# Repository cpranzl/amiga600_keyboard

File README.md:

# amiga600_keyboard
A replacement for the Amiga 600 keyboard

## Measurements

## OpenSCAD
linear_extrude(50){
    polygon(points=[[0,0],
                    [0,1245],
                    [3240,1240],
                    [3240,1005],
                    [3040,1005],
                    [3040,525],
                    [3240,525],
                    [3240,0]]
    );
}

## KiCAD

 40,  40   -  40, 164.5
 40, 164.5 - 364, 164.5
364, 164.5 - 364, 140.5
364, 140.5 - 344, 140.5
344, 140.5 - 344,  92.5
344,  92.5 - 364,  92.5
364,  92.5 - 364,  40
364,  40   -  40,  40

# Key Placement

Row 00  50.038
Row 01  78.994
Row 02  98.044
Row 03 117.094
Row 04 136.144
Row 05 155.067

Esc    57.023,  50.038
Help  347.472,  50.038
Del   350.012,  78.994
Up    330.581, 136.144
Left  311.531, 155.067
Down  330.581, 155.067
Right 349.631, 155.067

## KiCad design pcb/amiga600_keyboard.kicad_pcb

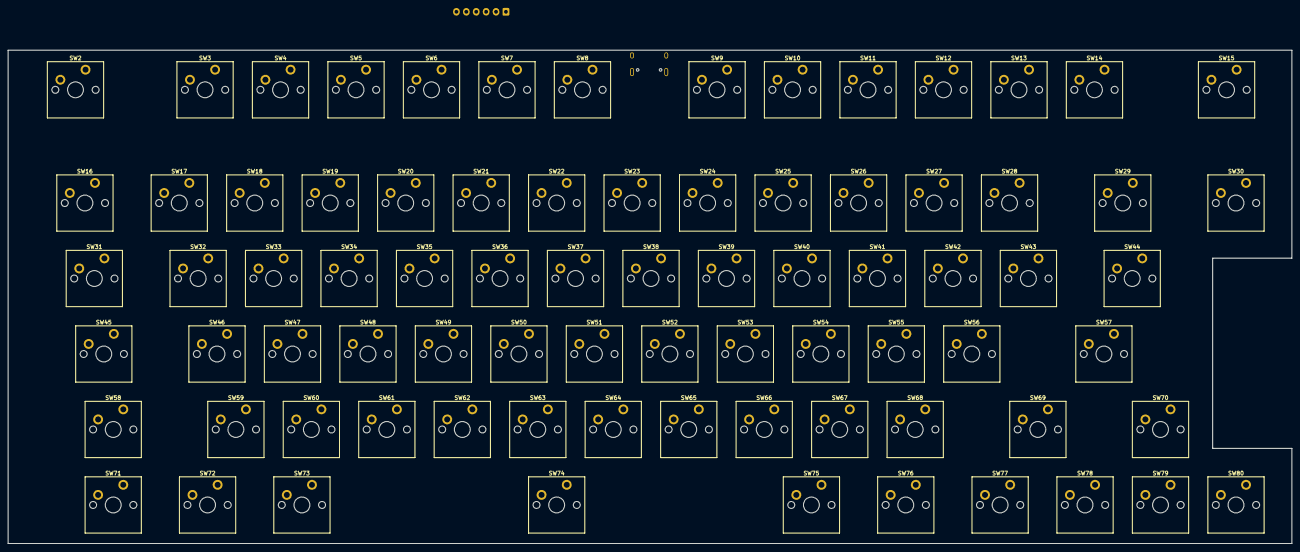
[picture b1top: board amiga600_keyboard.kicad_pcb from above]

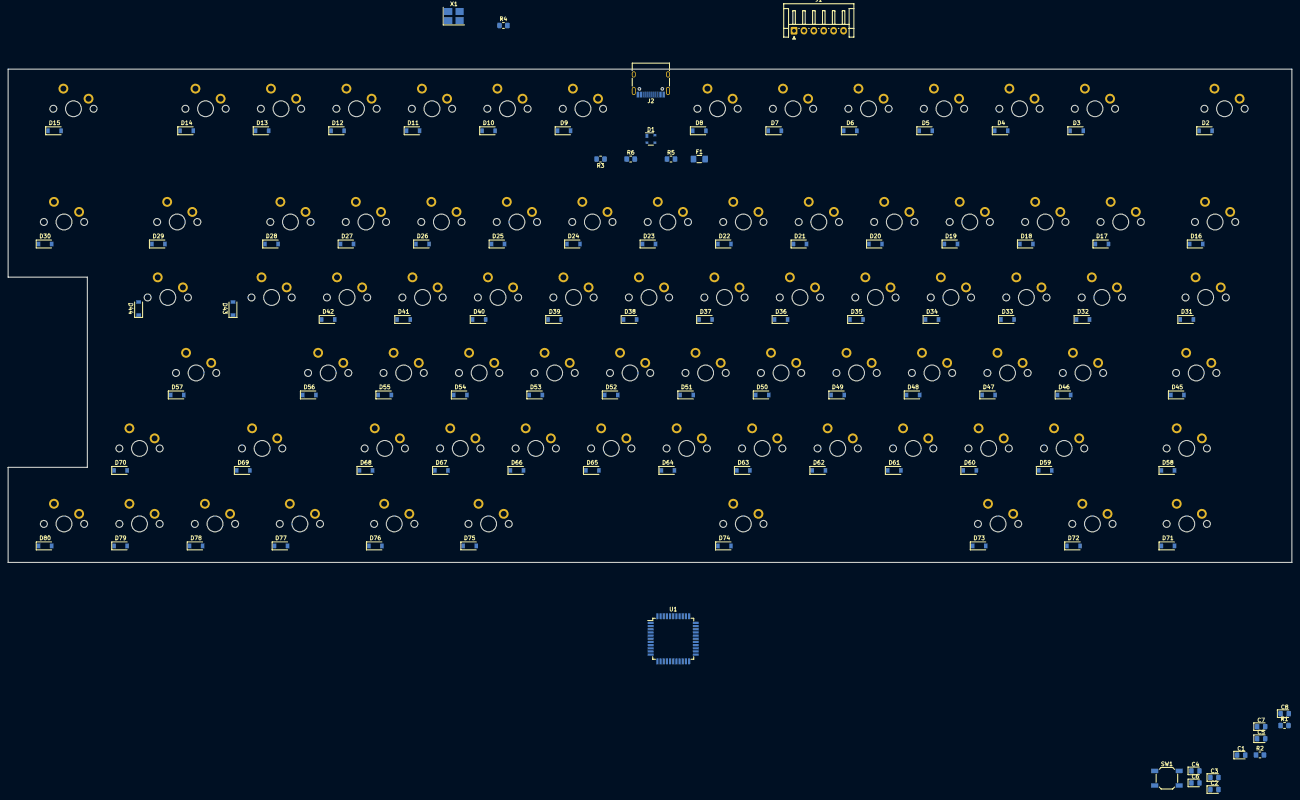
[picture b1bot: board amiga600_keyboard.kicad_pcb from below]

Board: 2 copper layers, 324.0 x 124.5 mm, 179 parts (100 on the bottom side), 117 nets, no tracks yet.

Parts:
C1, C2: 22p; D_0805_2012Metric_Pad1.15x1.40mm_HandSolder
C3, C4, C6, C7, C8: 0.1u; D_0805_2012Metric_Pad1.15x1.40mm_HandSolder
C5: 1u; D_0805_2012Metric_Pad1.15x1.40mm_HandSolder
D1: PRTR5V0U2X; SOT-143
D2, D3, D4, D5, D6, D7, D8, D9, D10, D11, D12, D13, D14, D15, D16, D17, D18, D19, D20, D21, D22, D23, D24, D25, D26, D27, D28, D29, D30, D31, D32, D33, D34, D35, D36, D37, D38, D39, D40, D41, D42, D43, D44, D45, D46, D47, D48, D49, D50, D51, D52, D53, D54, D55, D56, D57, D58, D59, D60, D61, D62, D63, D64, D65, D66, D67, D68, D69, D70, D71, D72, D73, D74, D75, D76, D77, D78, D79, D80: D_Small; D_SOD-123
F1: 500m; Fuse_1206_3216Metric_Pad1.42x1.75mm_HandSolder
J1: AVR-ISP-6; JST_EH_S6B-EH_1x06_P2.50mm_Horizontal
J2: USB_C_Receptacle_USB2.0; USB_C_Receptacle_HRO_TYPE-C-31-M-12
R1, R2: 10k; R_0805_2012Metric_Pad1.20x1.40mm_HandSolder
R3, R4: 5.1k; R_0805_2012Metric_Pad1.20x1.40mm_HandSolder
R5, R6: 22; R_0805_2012Metric_Pad1.20x1.40mm_HandSolder
SW1: SW_Push; SW_SPST_SKQG_WithoutStem
SW2: Esc; SW_Cherry_MX_PCB_1.25u
SW3: F1; SW_Cherry_MX_PCB_1.00u
SW4: F2; SW_Cherry_MX_PCB_1.00u
SW5: F3; SW_Cherry_MX_PCB_1.00u
SW6: F4; SW_Cherry_MX_PCB_1.00u
SW7: F5; SW_Cherry_MX_PCB_1.00u
SW8: F6; SW_Cherry_MX_PCB_1.00u
SW9: F7; SW_Cherry_MX_PCB_1.00u
SW10: F8; SW_Cherry_MX_PCB_1.00u
SW11: F9; SW_Cherry_MX_PCB_1.00u
SW12: F10; SW_Cherry_MX_PCB_1.00u
SW13: F11; SW_Cherry_MX_PCB_1.00u
SW14: F12; SW_Cherry_MX_PCB_1.00u
SW15: Help; SW_Cherry_MX_PCB_1.25u
SW16: Grv; SW_Cherry_MX_PCB_1.50u
SW17: 1; SW_Cherry_MX_PCB_1.00u
SW18: 2; SW_Cherry_MX_PCB_1.00u
SW19: 3; SW_Cherry_MX_PCB_1.00u
SW20: 4; SW_Cherry_MX_PCB_1.00u
SW21: 5; SW_Cherry_MX_PCB_1.00u
SW22: 6; SW_Cherry_MX_PCB_1.00u
SW23: 7; SW_Cherry_MX_PCB_1.00u
SW24: 8; SW_Cherry_MX_PCB_1.00u
SW25: 9; SW_Cherry_MX_PCB_1.00u
SW26: 0; SW_Cherry_MX_PCB_1.00u
SW27: -; SW_Cherry_MX_PCB_1.00u
SW28: =; SW_Cherry_MX_PCB_1.00u
SW29: Bksp; SW_Cherry_MX_PCB_2.00u
SW30: Del; SW_Cherry_MX_PCB_1.00u
SW31: Tab; SW_Cherry_MX_PCB_1.75u
SW32: Q; SW_Cherry_MX_PCB_1.00u
SW33: W; SW_Cherry_MX_PCB_1.00u
SW34: E; SW_Cherry_MX_PCB_1.00u
SW35: R; SW_Cherry_MX_PCB_1.00u
SW36: T; SW_Cherry_MX_PCB_1.00u
SW37: Y; SW_Cherry_MX_PCB_1.00u
SW38: U; SW_Cherry_MX_PCB_1.00u
SW39: I; SW_Cherry_MX_PCB_1.00u
SW40: O; SW_Cherry_MX_PCB_1.00u
SW41: P; SW_Cherry_MX_PCB_1.00u
SW42: [; SW_Cherry_MX_PCB_1.00u
SW43: ]; SW_Cherry_MX_PCB_1.00u
SW44: \; SW_Cherry_MX_PCB_1.75u
SW45: Hyper; SW_Cherry_MX_PCB_2.00u
SW46: A; SW_Cherry_MX_PCB_1.00u
SW47: S; SW_Cherry_MX_PCB_1.00u
SW48: D; SW_Cherry_MX_PCB_1.00u
SW49: F; SW_Cherry_MX_PCB_1.00u
SW50: G; SW_Cherry_MX_PCB_1.00u
SW51: H; SW_Cherry_MX_PCB_1.00u
SW52: J; SW_Cherry_MX_PCB_1.00u
SW53: K; SW_Cherry_MX_PCB_1.00u
SW54: L; SW_Cherry_MX_PCB_1.00u
SW55: ;; SW_Cherry_MX_PCB_1.00u
SW56: '; SW_Cherry_MX_PCB_1.00u
SW57: Enter; SW_Cherry_MX_PCB_2.50u
SW58: LShift; SW_Cherry_MX_PCB_2.25u
SW59: Z; SW_Cherry_MX_PCB_1.00u
SW60: X; SW_Cherry_MX_PCB_1.00u
SW61: C; SW_Cherry_MX_PCB_1.00u
SW62: V; SW_Cherry_MX_PCB_1.00u
SW63: B; SW_Cherry_MX_PCB_1.00u
SW64: N; SW_Cherry_MX_PCB_1.00u
SW65: M; SW_Cherry_MX_PCB_1.00u
SW66: ,; SW_Cherry_MX_PCB_1.00u
SW67: .; SW_Cherry_MX_PCB_1.00u
SW68: /; SW_Cherry_MX_PCB_1.00u
SW69: RShift; SW_Cherry_MX_PCB_2.25u
SW70: Up; SW_Cherry_MX_PCB_1.00u
SW71: Ctrl; SW_Cherry_MX_PCB_1.25u
SW72: LAlt; SW_Cherry_MX_PCB_1.25u
SW73: LAmiga; SW_Cherry_MX_PCB_1.25u
SW74: Space; SW_Cherry_MX_PCB_5.50u
SW75: RAmiga; SW_Cherry_MX_PCB_1.25u
SW76: RAlt; SW_Cherry_MX_PCB_1.25u
SW77: Fn; SW_Cherry_MX_PCB_1.25u
SW78: Left; SW_Cherry_MX_PCB_1.00u
SW79: Down; SW_Cherry_MX_PCB_1.00u
SW80: Right; SW_Cherry_MX_PCB_1.00u
U1: ATmega32U4-A; TQFP-44_10x10mm_P0.8mm
X1: XTAL; Crystal_SMD_3225-4Pin_3.2x2.5mm_HandSoldering

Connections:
+5V: C3.1, C4.1, C6.1, C7.1, C8.1, F1.2, J1.2 (VCC), R2.1, U1.2 (UVCC), U1.7 (VBUS), U1.14 (VCC), U1.24 (AVCC), U1.34 (VCC), U1.44 (AVCC)
COL 00: D2.1 (K), D3.1 (K), D4.1 (K), D5.1 (K), D6.1 (K), D7.1 (K), D8.1 (K), D9.1 (K), D10.1 (K), D11.1 (K), D12.1 (K), D13.1 (K), D14.1 (K), D15.1 (K), SW2.2, SW16.2, SW31.2, SW45.2, SW58.2, SW71.2, U1.1 (PE6), U1.28 (PB4)
COL 0A: SW11.2, SW26.2, SW40.2, SW53.2, SW67.2, SW75.2, U1.21 (PD3)
COL 0B: SW12.2, SW27.2, SW41.2, SW54.2, SW68.2, SW76.2, U1.22 (PD5)
COL 0C: SW13.2, SW28.2, SW42.2, SW55.2, SW69.2, SW77.2, U1.25 (PD4)
COL 0D: SW14.2, SW29.2, SW43.2, SW56.2, SW78.2, U1.26 (PD6)
COL 0E: SW30.2, SW44.2, SW57.2, SW70.2, SW79.2, U1.27 (PD7)
COL 0F: SW15.2, SW80.2, U1.18 (PD0)
COL 01: SW17.2, SW72.2, U1.29 (PB5)
COL 02: SW3.2, SW18.2, SW32.2, SW59.2, SW73.2, U1.30 (PB6)
COL 03: SW4.2, SW19.2, SW33.2, SW46.2, SW60.2, U1.31 (PC6)
COL 04: SW5.2, SW20.2, SW34.2, SW47.2, SW61.2, U1.32 (PC7)
COL 05: SW6.2, SW21.2, SW35.2, SW48.2, SW62.2, U1.37 (PF6)
COL 06: SW7.2, SW22.2, SW36.2, SW49.2, SW63.2, SW74.2, U1.36 (PF7)
COL 07: SW8.2, SW23.2, SW37.2, SW50.2, SW64.2, U1.8 (PB0)
COL 08: SW9.2, SW24.2, SW38.2, SW51.2, SW65.2, U1.19 (PD1)
COL 09: SW10.2, SW25.2, SW39.2, SW52.2, SW66.2, U1.20 (PD2)
D+: R6.2, U1.4 (D+)
D-: R5.1, U1.3 (D-)
DN: D1.3 (I/O2), J2.A7 (D-), J2.B7 (D-), R5.2
DP: D1.2 (I/O1), J2.A6 (D+), J2.B6 (D+), R6.1
GND: C1.2, C2.2, C3.2, C4.2, C5.2, C6.2, C7.2, C8.2, D1.1 (GND), J1.6 (GND), J2.A1 (GND), J2.A12 (GND), J2.B1 (GND), J2.B12 (GND), J2.S1 (SHIELD), R1.1, R3.2, R4.2, SW1.1, U1.5 (UGND), U1.15 (GND), U1.23 (GND), U1.35 (GND), U1.43 (GND), X1.2, X1.4
MISO: J1.1 (MISO), U1.11 (PB3)
MOSI: J1.4 (MOSI), U1.10 (PB2)
unnamed: C5.1, U1.6 (UCAP)
unnamed: D2.2 (A), SW2.1
unnamed: D3.2 (A), SW3.1
unnamed: D4.2 (A), SW4.1
unnamed: D5.2 (A), SW5.1
unnamed: D6.2 (A), SW6.1
unnamed: D7.2 (A), SW7.1
unnamed: D8.2 (A), SW8.1
unnamed: D9.2 (A), SW9.1
unnamed: D10.2 (A), SW10.1
unnamed: D11.2 (A), SW11.1
unnamed: D12.2 (A), SW12.1
unnamed: D13.2 (A), SW13.1
unnamed: D14.2 (A), SW14.1
unnamed: D15.2 (A), SW15.1
unnamed: D16.2 (A), SW16.1
unnamed: D17.2 (A), SW17.1
unnamed: D18.2 (A), SW18.1
unnamed: D19.2 (A), SW19.1
unnamed: D20.2 (A), SW20.1
unnamed: D21.2 (A), SW21.1
unnamed: D22.2 (A), SW22.1
unnamed: D23.2 (A), SW23.1
unnamed: D24.2 (A), SW24.1
unnamed: D25.2 (A), SW25.1
unnamed: D26.2 (A), SW26.1
unnamed: D27.2 (A), SW27.1
unnamed: D28.2 (A), SW28.1
unnamed: D29.2 (A), SW29.1
unnamed: D30.2 (A), SW30.1
unnamed: D31.2 (A), SW31.1
unnamed: D32.2 (A), SW32.1
unnamed: D33.2 (A), SW33.1
unnamed: D34.2 (A), SW34.1
unnamed: D35.2 (A), SW35.1
unnamed: D36.2 (A), SW36.1
unnamed: D37.2 (A), SW37.1
unnamed: D38.2 (A), SW38.1
unnamed: D39.2 (A), SW39.1
unnamed: D40.2 (A), SW40.1
unnamed: D41.2 (A), SW41.1
unnamed: D42.2 (A), SW42.1
unnamed: D43.2 (A), SW43.1
unnamed: D44.2 (A), SW44.1
unnamed: D45.2 (A), SW45.1
unnamed: D46.2 (A), SW46.1
unnamed: D47.2 (A), SW47.1
unnamed: D48.2 (A), SW48.1
unnamed: D49.2 (A), SW49.1
unnamed: D50.2 (A), SW50.1
unnamed: D51.2 (A), SW51.1
unnamed: D52.2 (A), SW52.1
unnamed: D53.2 (A), SW53.1
unnamed: D54.2 (A), SW54.1
unnamed: D55.2 (A), SW55.1
unnamed: D56.2 (A), SW56.1
unnamed: D57.2 (A), SW57.1
unnamed: D58.2 (A), SW58.1
unnamed: D59.2 (A), SW59.1
unnamed: D60.2 (A), SW60.1
unnamed: D61.2 (A), SW61.1
unnamed: D62.2 (A), SW62.1
unnamed: D63.2 (A), SW63.1
unnamed: D64.2 (A), SW64.1
unnamed: D65.2 (A), SW65.1
unnamed: D66.2 (A), SW66.1
unnamed: D67.2 (A), SW67.1
unnamed: D68.2 (A), SW68.1
unnamed: D69.2 (A), SW69.1
unnamed: D70.2 (A), SW70.1
unnamed: D71.2 (A), SW71.1
unnamed: D72.2 (A), SW72.1
unnamed: D73.2 (A), SW73.1
unnamed: D74.2 (A), SW74.1
unnamed: D75.2 (A), SW75.1
unnamed: D76.2 (A), SW76.1
unnamed: D77.2 (A), SW77.1
unnamed: D78.2 (A), SW78.1
unnamed: D79.2 (A), SW79.1
unnamed: D80.2 (A), SW80.1
unnamed: J2.A5 (CC1), R3.1
unnamed: J2.B5 (CC2), R4.1
unnamed: R1.2, U1.33 (~HWB/PE2)
RESET: J1.5 (~RST), R2.2, SW1.2, U1.13 (~RESET)
ROW 01: D16.1 (K), D17.1 (K), D18.1 (K), D19.1 (K), D20.1 (K), D21.1 (K), D22.1 (K), D23.1 (K), D24.1 (K), D25.1 (K), D26.1 (K), D27.1 (K), D28.1 (K), D29.1 (K), D30.1 (K), U1.12 (PB7)
ROW 02: D31.1 (K), D32.1 (K), D33.1 (K), D34.1 (K), D35.1 (K), D36.1 (K), D37.1 (K), D38.1 (K), D39.1 (K), D40.1 (K), D41.1 (K), D42.1 (K), D43.1 (K), D44.1 (K), U1.41 (PF0)
ROW 03: D45.1 (K), D46.1 (K), D47.1 (K), D48.1 (K), D49.1 (K), D50.1 (K), D51.1 (K), D52.1 (K), D53.1 (K), D54.1 (K), D55.1 (K), D56.1 (K), D57.1 (K), U1.40 (PF1)
ROW 04: D58.1 (K), D59.1 (K), D60.1 (K), D61.1 (K), D62.1 (K), D63.1 (K), D64.1 (K), D65.1 (K), D66.1 (K), D67.1 (K), D68.1 (K), D69.1 (K), D70.1 (K), U1.39 (PF4)
ROW 05: D71.1 (K), D72.1 (K), D73.1 (K), D74.1 (K), D75.1 (K), D76.1 (K), D77.1 (K), D78.1 (K), D79.1 (K), D80.1 (K), U1.38 (PF5)
SCK: J1.3 (SCK), U1.9 (PB1)
VCC: D1.4 (VCC), F1.1, J2.A4 (VBUS), J2.A9 (VBUS), J2.B4 (VBUS), J2.B9 (VBUS)
XTAL1: C1.1, U1.17 (XTAL1), X1.1
XTAL2: C2.1, U1.16 (XTAL2), X1.3

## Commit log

2022-04-15 Initial commit.
2022-05-12 Schematics done, pcb in the work.
2023-05-15 PCBs in the work
